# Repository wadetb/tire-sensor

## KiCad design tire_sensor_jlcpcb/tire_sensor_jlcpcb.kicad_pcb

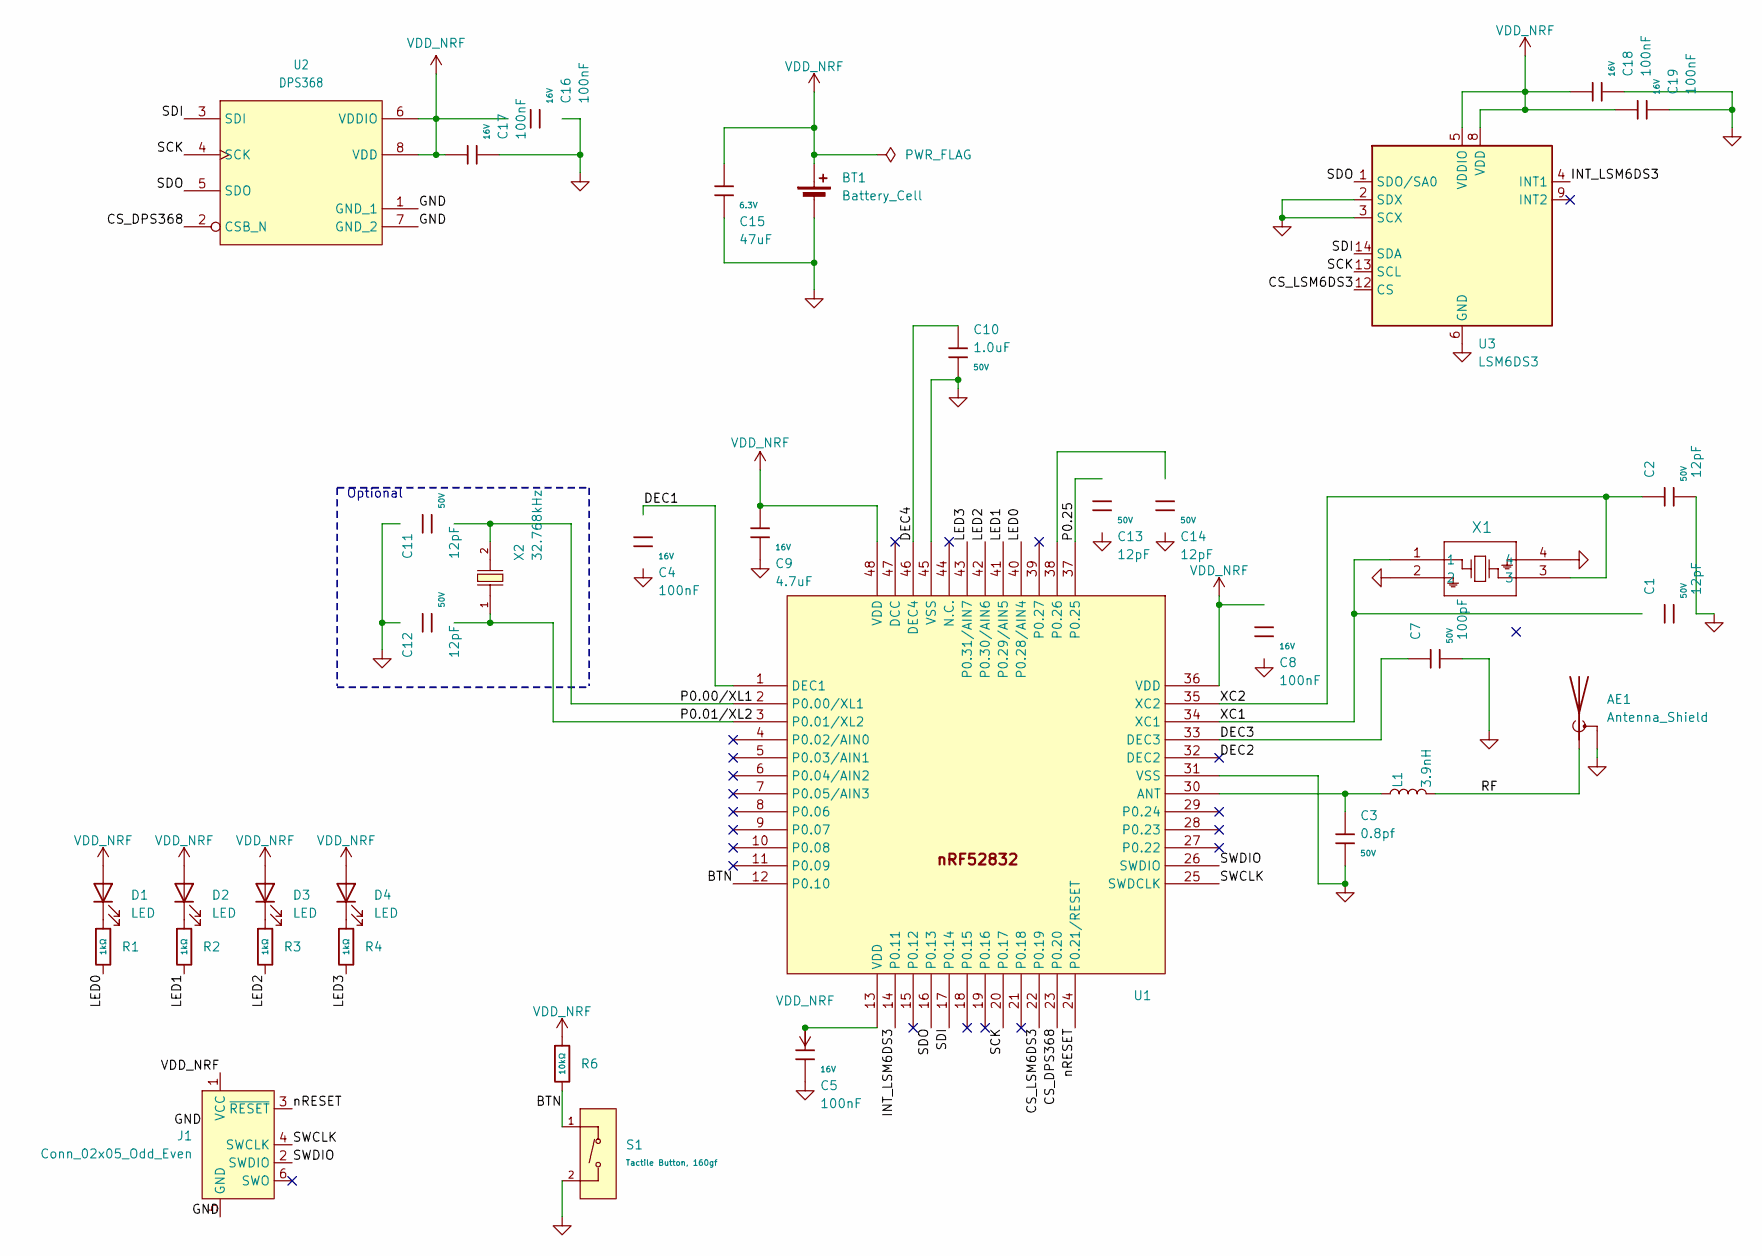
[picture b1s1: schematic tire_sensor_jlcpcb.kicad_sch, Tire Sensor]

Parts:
AE1: Antenna_Shield; Texas_SWRA117D_2.4GHz_Left
BT1: Battery_Cell; BatteryHolder_Renata_SMTU2032-LF_1x2032
C1, C2, C11, C12, C13, C14: 12pF; C_0402; Voltage Rated 50V; Tolerance ±5%; PART NUMBER C0402-12p; LCSC C1547
C3: 0.8pf; C_0402; Voltage Rated 50V; PART NUMBER C0402-0.8p; LCSC C1550
C4, C5, C8: 100nF; C_0402; Voltage Rated 16V; Tolerance ±10%; PART NUMBER C0402-100n; LCSC C1525
C7: 100pF; C_0402; Voltage Rated 50V; Tolerance ±5%; PART NUMBER C0402-100p; LCSC C1546
C9: 4.7uF; C_0603; Voltage Rated 16V; Tolerance ±10%; PART NUMBER C0603-4µ7; LCSC C19666
C10: 1.0uF; C_0603; Voltage Rated 50V; Tolerance ±10%; PART NUMBER C0603-1µ0; LCSC C15849
C15: 47uF; C_0805; Voltage Rated 6.3V; Tolerance ±20%; PART NUMBER C0402-12p; LCSC C16780
C16, C17, C19: 100nF; C_0402; Voltage Rated 16V; Tolerance ±10%; PART NUMBER C0402-12p; LCSC C1525
C18: 100nF; C_0402; Tolerance ±10%; Rated Voltage 6.3V; PART NUMBER C0402-12p; LCSC C1525
D1, D2, D3, D4: LED; LED_0603_1608Metric
J1: Conn_02x05_Odd_Even; Tag-Connect_TC2030-IDC-NL_2x03_P1.27mm_Vertical
L1: 3.9nH; L_0402; PART NUMBER L0402-3n9; LCSC C14033
R1, R2, R3, R4: 1kΩ; R_0402; Overload Voltage (Max) 50V; Tolerance ±1%; Part 0402WGF1001TCE; LCSC C11702
R6: 10kΩ; R_0402; Overload Voltage (Max) 50V; Tolerance ±1%; Part 0402WGF1002TCE; LCSC C25744
S1: Tactile Button, 160gf; SW_TS-1088-AR02016; Voltage Rating (Dc) 12V; Part TS-1088-AR02016; LCSC C720477
U1: QFN-48-1EP_6x6mm_P0.4mm_EP4.6x4.6mm_ThermalVias; PART NUMBER nRF52832-QFAA
U2: DPS368; LGA8S145X65P2X4_200X250X110-V
U3: LSM6DS3; LGA-14_3x2.5mm_P0.5mm_LayoutBorder3x4y; PARTREV 2
X1: NX2016SA-32MHZ-EXS00A-CS06654; FA-128_EPS
X2: 32.768kHz; FC-135R_L3.2-W1.5; Frequency Tolerance ±20ppm; PART NUMBER XTAL_SMD3215_32.768kHz_9pF_General; LCSC C32346

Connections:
/BTN: R6.2, S1.1 (A), U1.12 (P0.10)
/CS_DPS368: U1.23 (P0.20), U2.2 (CSB_N)
/CS_LSM6DS3: U1.22 (P0.19), U3.12 (CS)
/DEC1: C4.1, U1.1 (DEC1)
/DEC2: U1.32 (DEC2)
/DEC3: C7.1, U1.33 (DEC3)
/DEC4: C10.1, U1.46 (DEC4)
/INT_LSM6DS3: U1.14 (P0.11), U3.4 (INT1)
/LED0: R1.2, U1.40 (P0.28/AIN4)
/LED1: R2.2, U1.41 (P0.29/AIN5)
/LED2: R3.2, U1.42 (P0.30/AIN6)
/LED3: R4.2, U1.43 (P0.31/AIN7)
/P0.00/XL1: C11.2, U1.2 (P0.00/XL1), X2.2
/P0.01/XL2: C12.2, U1.3 (P0.01/XL2), X2.1
/P0.25: C13.1, U1.37 (P0.25)
/RF: AE1.1 (A), L1.2
/SCK: U1.20 (P0.17), U2.4 (SCK), U3.13 (SCL)
/SDI: U1.17 (P0.14), U2.3 (SDI), U3.14 (SDA)
/SDO: U1.16 (P0.13), U2.5 (SDO), U3.1 (SDO/SA0)
/SWCLK: J1.4 (SWCLK), U1.25 (SWDCLK)
/SWDIO: J1.2 (SWDIO), U1.26 (SWDIO)
/XC1: C1.1, U1.34 (XC1), X1.1
/XC2: C2.1, U1.35 (XC2), X1.3
/nRESET: J1.3 (~RESET), U1.24 (P0.21/RESET)
GND: AE1.2 (Shield), BT1.2 (-), C1.2, C2.2, C3.2, C4.2, C5.2, C7.2, C8.2, C9.2, C10.2, C11.1, C12.1, C13.2, C14.2, C15.2, C16.2, C17.2, C18.2, C19.2, J1.5 (GND), S1.2 (B), U1.31 (VSS), U1.45 (VSS), U1.49 (GND), U2.1 (GND_1), U2.7 (GND_2), U3.2 (SDX), U3.3 (SCX), U3.6 (GND), U3.7 (GND), X1.2, X1.4
unnamed: D1.1 (K), R1.1
unnamed: D2.1 (K), R2.1
unnamed: D3.1 (K), R3.1
unnamed: D4.1 (K), R4.1
unnamed: C3.1, L1.1, U1.30 (ANT)
unnamed: C14.1, U1.38 (P0.26)
VDD_NRF: BT1.1 (+), C5.1, C8.1, C9.1, C15.1, C16.1, C17.1, C18.1, C19.1, D1.2 (A), D2.2 (A), D3.2 (A), D4.2 (A), J1.1 (VCC), R6.1, U1.13 (VDD), U1.36 (VDD), U1.48 (VDD), U2.6 (VDDIO), U2.8 (VDD), U3.5 (VDDIO), U3.8 (VDD)

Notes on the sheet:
Optional

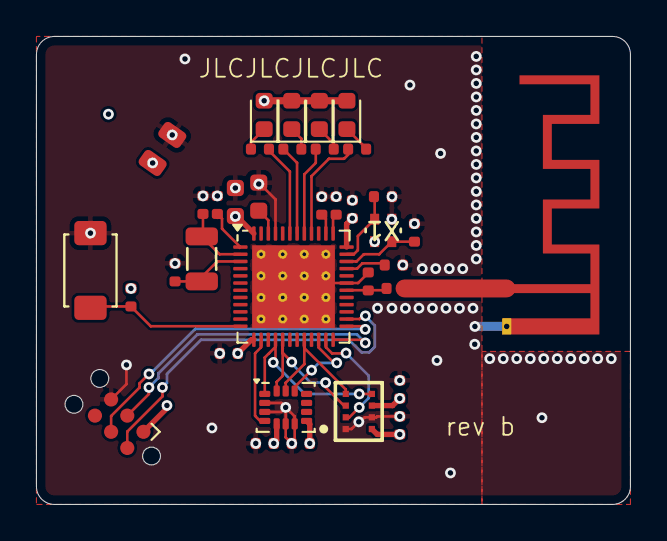
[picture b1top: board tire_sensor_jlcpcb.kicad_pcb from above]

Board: 4 copper layers, 33.0 x 26.0 mm, 37 parts (1 on the bottom side), 31 nets.

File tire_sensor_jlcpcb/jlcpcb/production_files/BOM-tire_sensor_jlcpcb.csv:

Comment,Designator,Footprint,LCSC,Quantity
1kΩ,"R1,R2,R3,R4",R_0402,C11702,4
3.9nH,L1,L_0402,C14033,1
100nF,"C16,C17,C18,C19,C4,C5,C8",C_0402,C1525,7
100pF,C7,C_0402,C1546,1
12pF,"C1,C11,C12,C13,C14,C2",C_0402,C1547,6
0.8pf,C3,C_0402,C1550,1
1.0uF,C10,C_0603,C15849,1
47uF,C15,C_0805,C16780,1
4.7uF,C9,C_0603,C19666,1
LED,"D2,D4",LED_0603_1608Metric,C2286,2
LED,"D1,D3",LED_0603_1608Metric,C2290,2
10kΩ,R6,R_0402,C25744,1
DPS368,U2,LGA8S145X65P2X4_200X250X110-V,C3232508,1
32.768kHz,X2,FC-135R_L3.2-W1.5,C32346,1
"Tactile Button, 160gf",S1,SW_TS-1088-AR02016,C720477,1
~,U1,QFN-48-1EP_6x6mm_P0.4mm_EP4.6x4.6mm_ThermalVias,C77540,1
NX2016SA-32MHZ-EXS00A-CS06654,X1,FA-128_EPS,C843260,1
LSM6DS3,U3,LGA-14_3x2.5mm_P0.5mm_LayoutBorder3x4y,C967633,1

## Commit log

2025-07-10 Initial commit - basic routing and JLCPCB setup but not final
2025-07-10 Move ground plane to In1.Cu for RF
2025-07-10 Update JLCPCB part assignments
2025-07-10 JCLPCB updated Crystal per stock, other fixes
2025-07-11 No uFL, LEDs, button
2025-07-11 PCB tweaks
2025-07-11 Schematic saved
2025-07-15 Add OSHPark version, wider spacing
2025-07-15 Fix VDD decoupling, reference docs
2025-07-16 Models, better decoupling
2025-07-16 Add images
2025-08-22 JLCPCB order W2025082300401265
2025-08-22 README
2025-08-22 Better routing and decoupling, reomved unused cap
2025-08-22 Added extra GND trace
2025-08-23 Add gyro, reroute sensors
2025-11-13 JLCPCB order W2025111310437228
2025-11-16 RF trace fixes from DevZone
2025-11-16 RF antenna tweaks
2025-11-16 Move via
2025-11-16 Zone clearance, refernce docs
2025-11-20 JLCPCB order W2025111621247668
2026-01-19 Swap crystal to FA-128 and regen fab outputs
